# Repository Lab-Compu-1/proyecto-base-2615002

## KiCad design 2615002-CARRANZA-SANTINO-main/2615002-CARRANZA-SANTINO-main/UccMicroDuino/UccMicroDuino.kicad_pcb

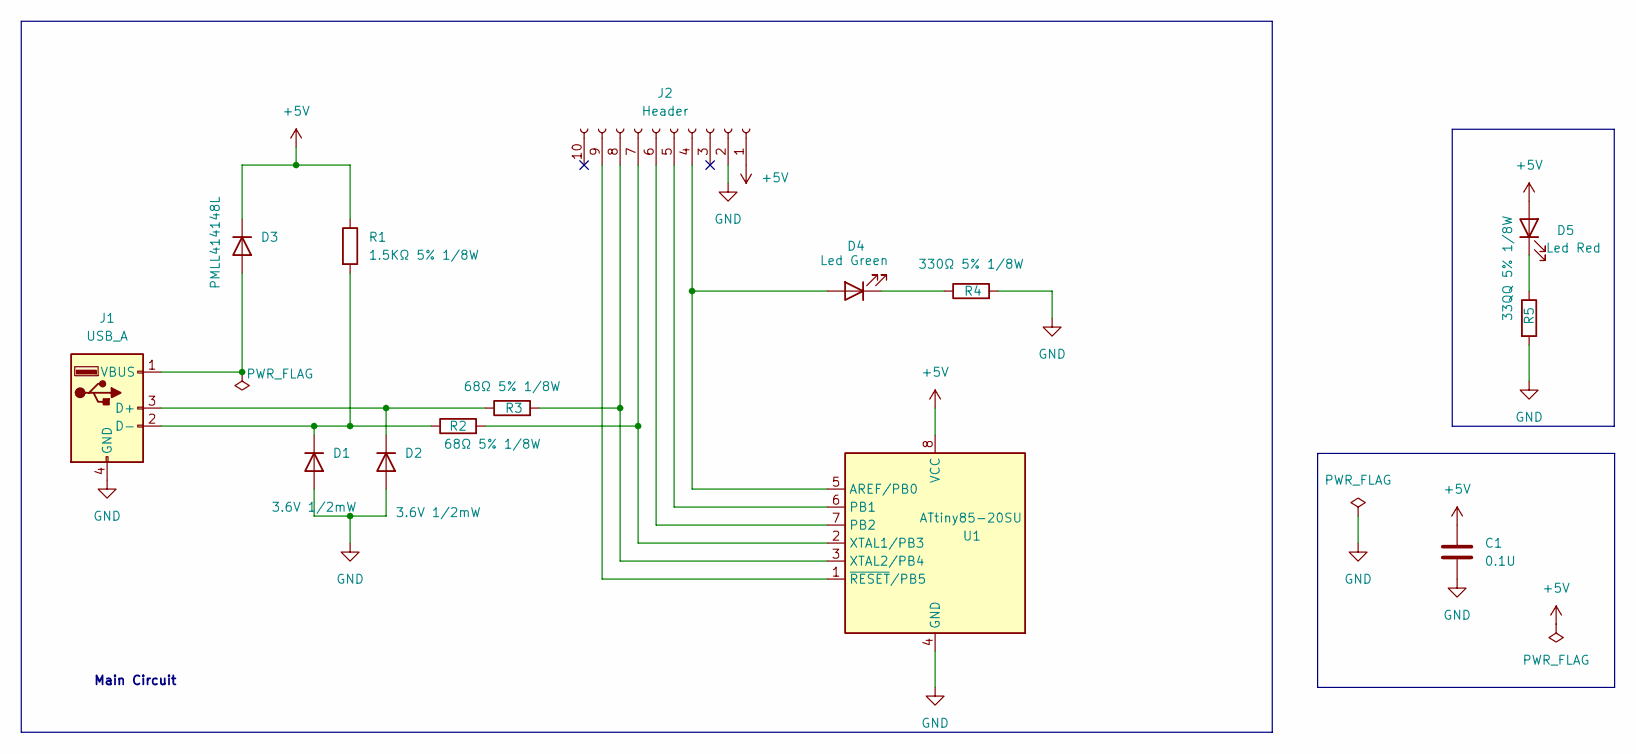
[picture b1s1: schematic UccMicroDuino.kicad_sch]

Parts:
C1: 0.1U; C_0805_2012Metric_Pad1.18x1.45mm_HandSolder
D1: 3.6V 1/2mW; D_MELF_Handsoldering
D2: 3.6V 1/2mW; D_SOD-123
D3: PMLL414148L; D_SOD-123
D4: Led Green; ledSMD
D5: Led Red; ledSMD
J1: USB_A; USB_A_UCC
J2: Header; PinHeader_1x10_P2.54mm_Vertical
R1: 1.5KΩ 5% 1/8W; R_0805_2012Metric_Pad1.20x1.40mm_HandSolder
R2, R3: 68Ω 5% 1/8W; R_0805_2012Metric_Pad1.20x1.40mm_HandSolder
R4: 330Ω 5% 1/8W; R_0805_2012Metric_Pad1.20x1.40mm_HandSolder
R5: 33QQ 5% 1/8W; R_0805_2012Metric_Pad1.20x1.40mm_HandSolder
U1: ATtiny85-20SU; SOIC-8W_5.3x5.3mm_P1.27mm

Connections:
+5V: C1.1, D3.1 (K), D5.2 (A), J2.1, R1.1, U1.8 (VCC)
GND: C1.2, D1.2 (A), D2.2 (A), J1.4 (GND), J2.2, R4.2, R5.2, U1.4 (GND)
unnamed: D1.1 (K), J1.2 (D-), R1.2, R2.1
unnamed: D2.1 (K), J1.3 (D+), R3.1
unnamed: D3.2 (A), J1.1 (VBUS)
unnamed: D4.2 (A), J2.4, U1.5 (AREF/PB0)
unnamed: D4.1 (K), R4.1
unnamed: D5.1 (K), R5.1
unnamed: J2.5, U1.6 (PB1)
unnamed: J2.6, U1.7 (PB2)
unnamed: J2.7, R2.2, U1.2 (XTAL1/PB3)
unnamed: J2.8, R3.2, U1.3 (XTAL2/PB4)
unnamed: J2.9, U1.1 (~RESET/PB5)

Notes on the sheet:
Main Circuit

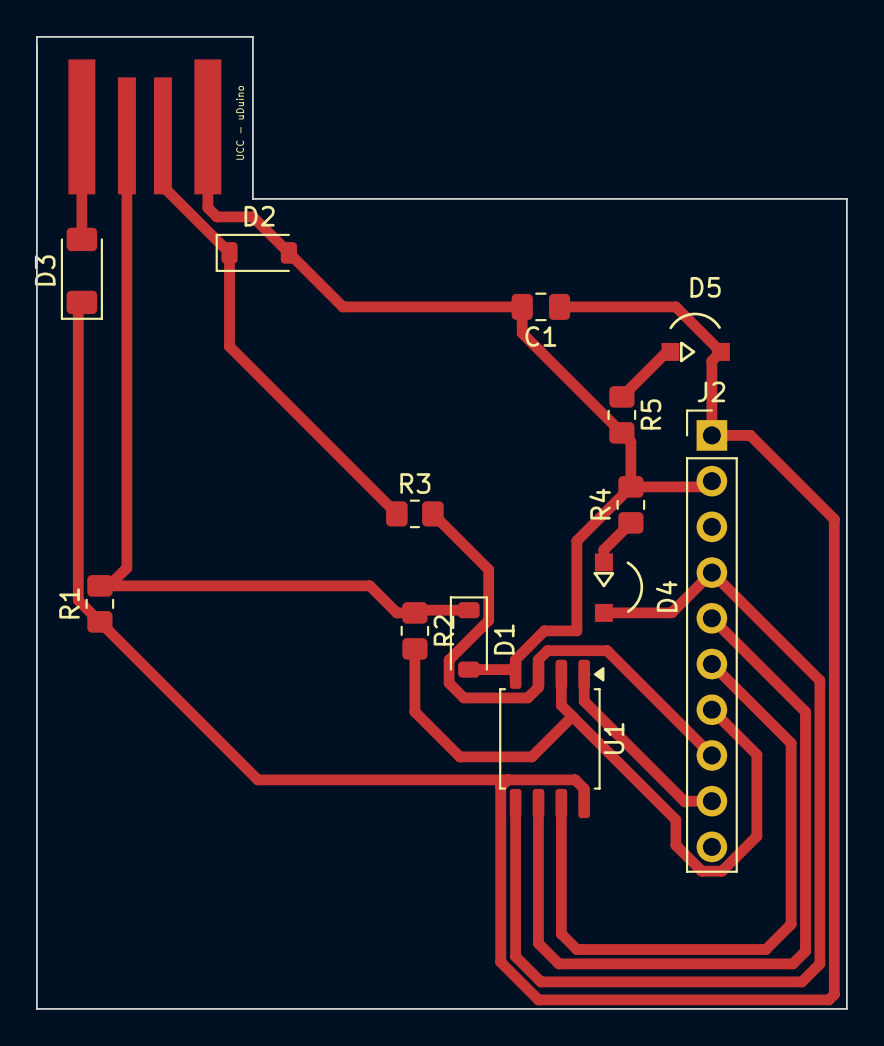
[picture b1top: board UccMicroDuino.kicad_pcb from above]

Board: 2 copper layers, 45.0 x 54.0 mm, 14 parts (0 on the bottom side), 13 nets.

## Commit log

2026-05-18 GitHub Classroom Feedback
2026-05-18 Setting up GitHub Classroom Feedback
2026-05-18 2615002-mi primer versionado con gitBash
2026-05-25 2615002- correcion de la placa kicad
2026-05-31 2615002-mi primer versionado de gitbash (correccion placa)
2026-06-01 2615002- mi primer versionado con gitBash (placa finalizada)
